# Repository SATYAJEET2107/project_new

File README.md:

# project_new
second circuit design board

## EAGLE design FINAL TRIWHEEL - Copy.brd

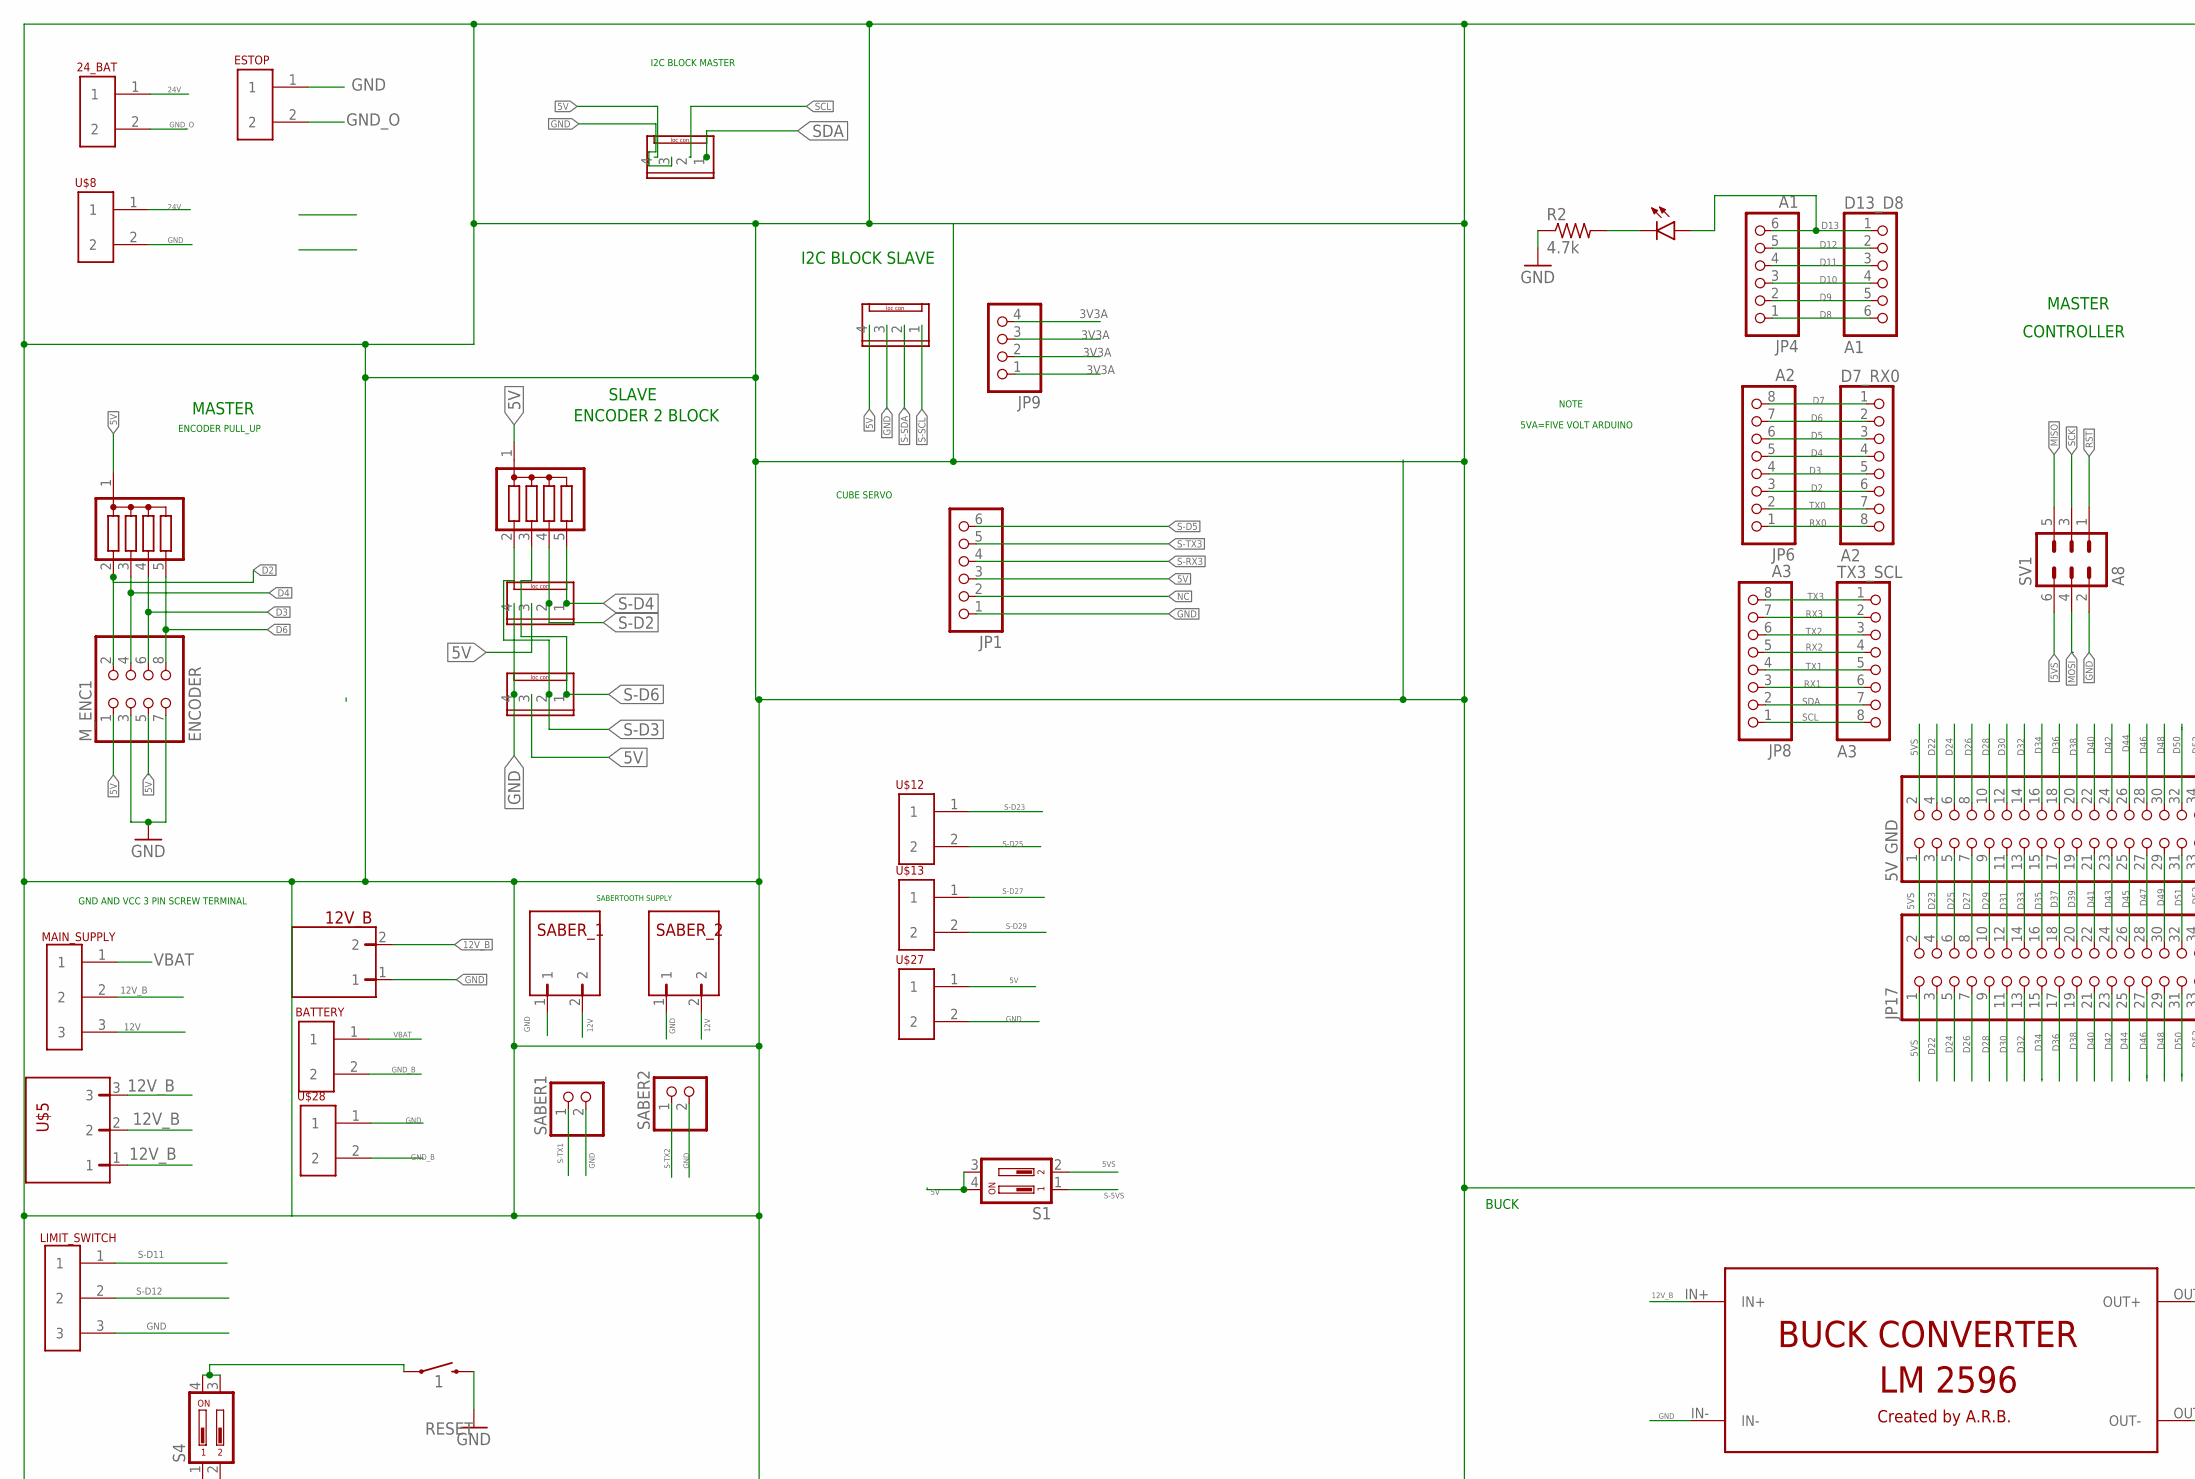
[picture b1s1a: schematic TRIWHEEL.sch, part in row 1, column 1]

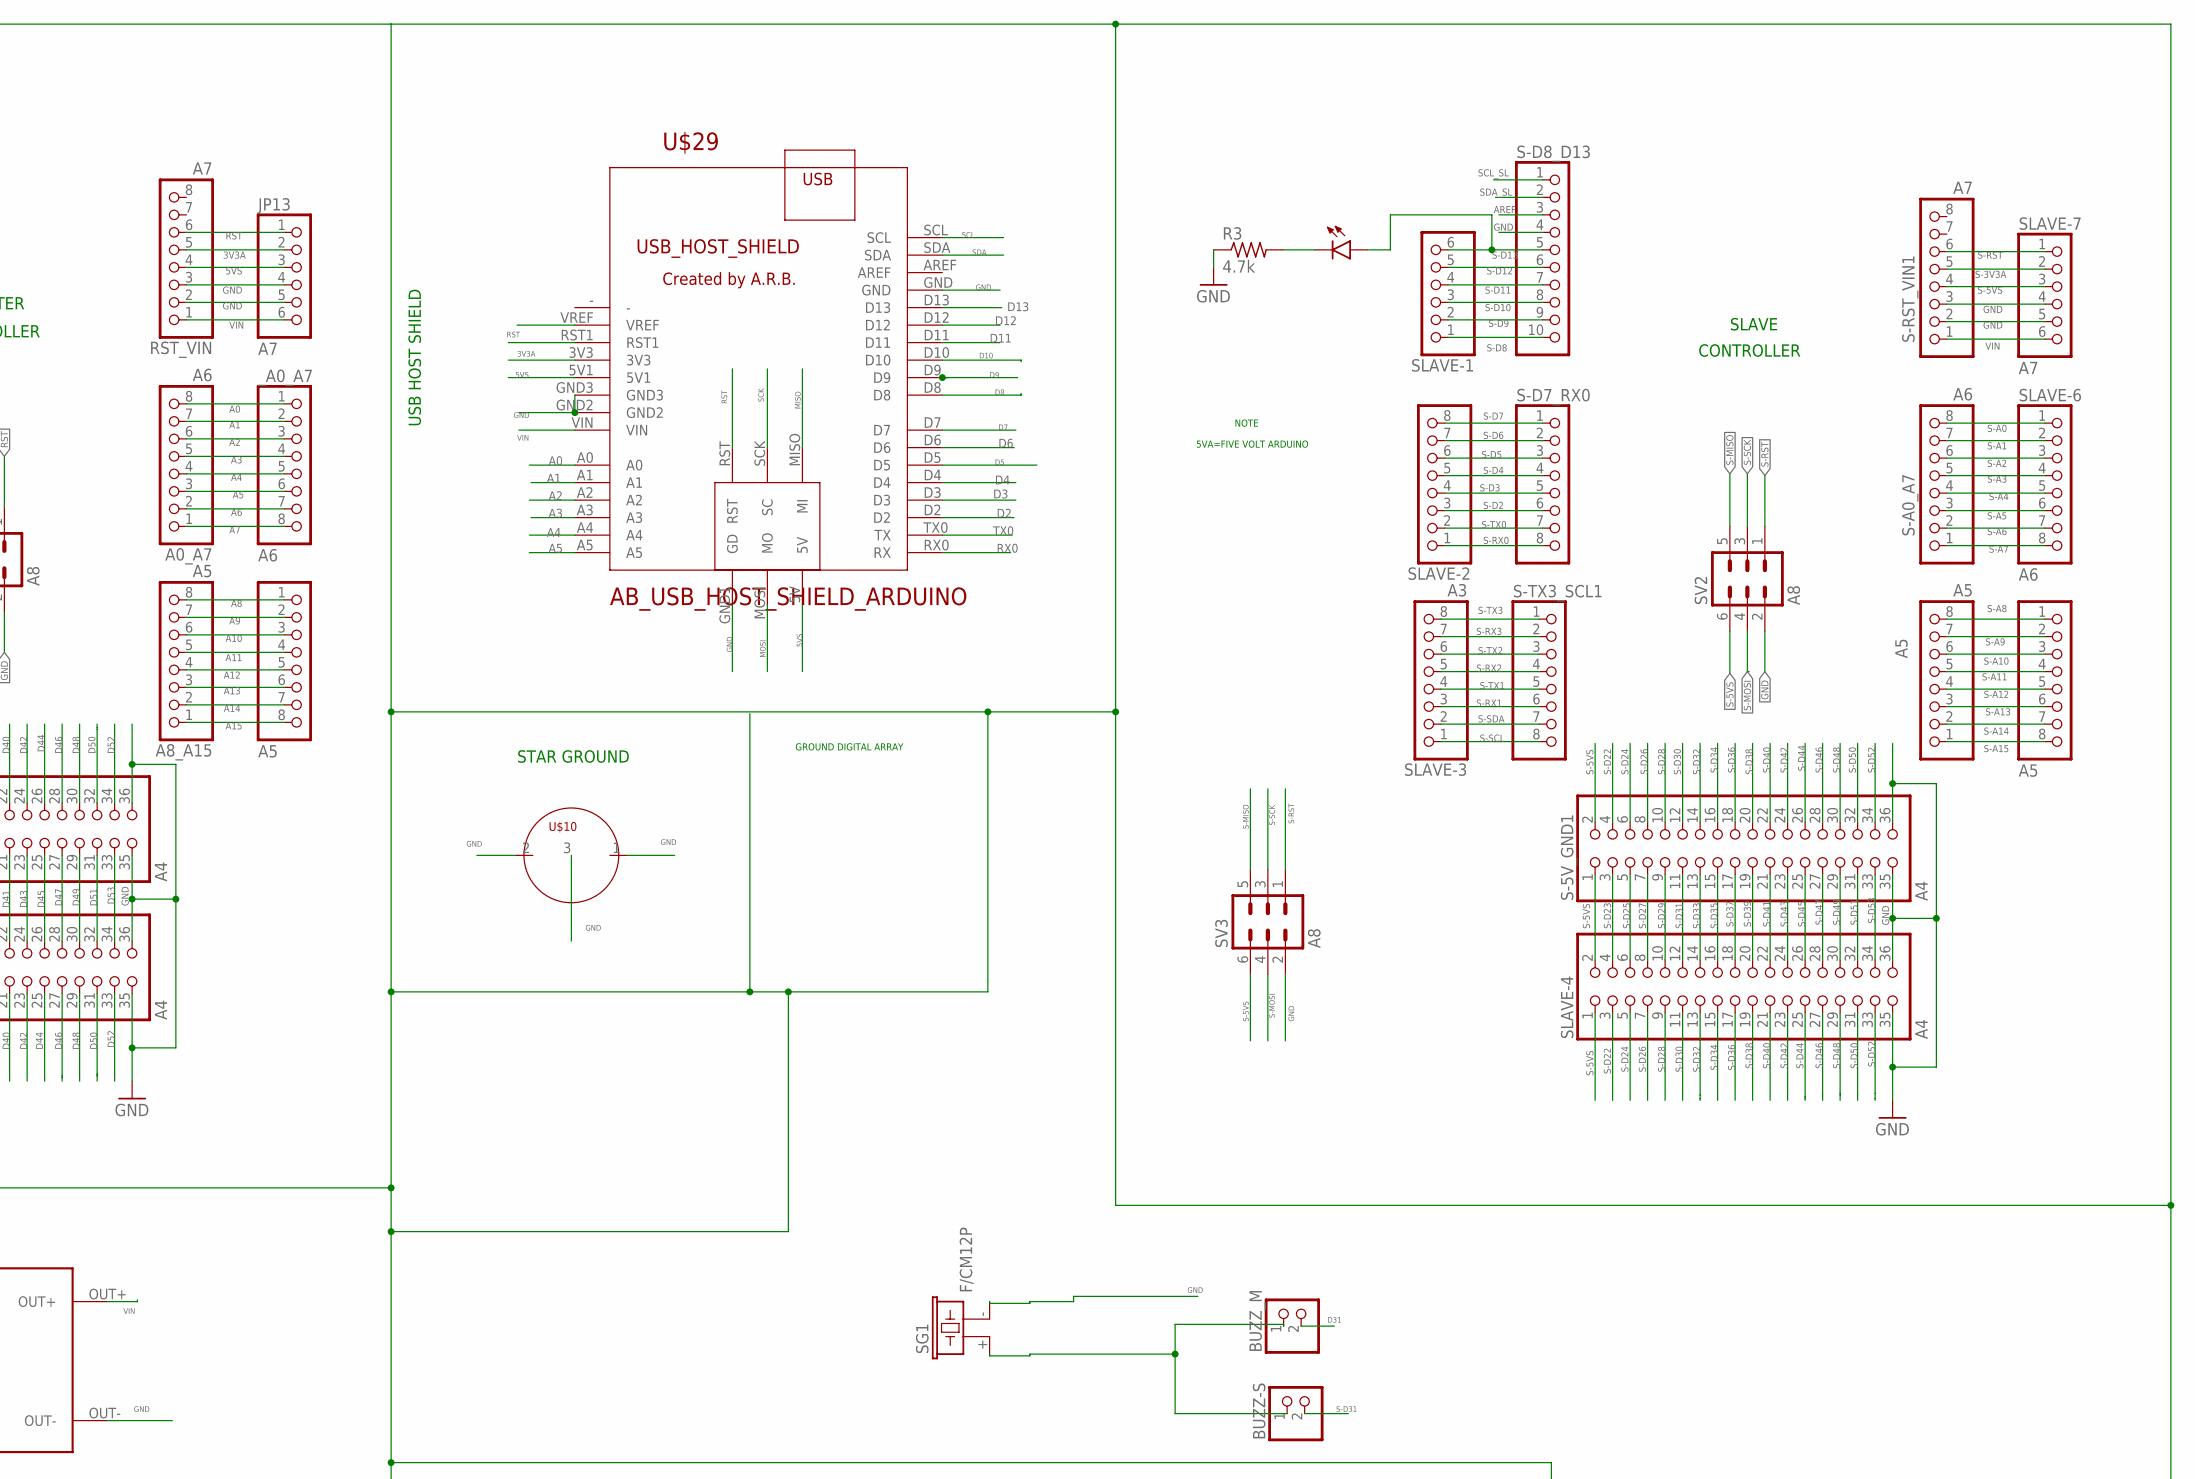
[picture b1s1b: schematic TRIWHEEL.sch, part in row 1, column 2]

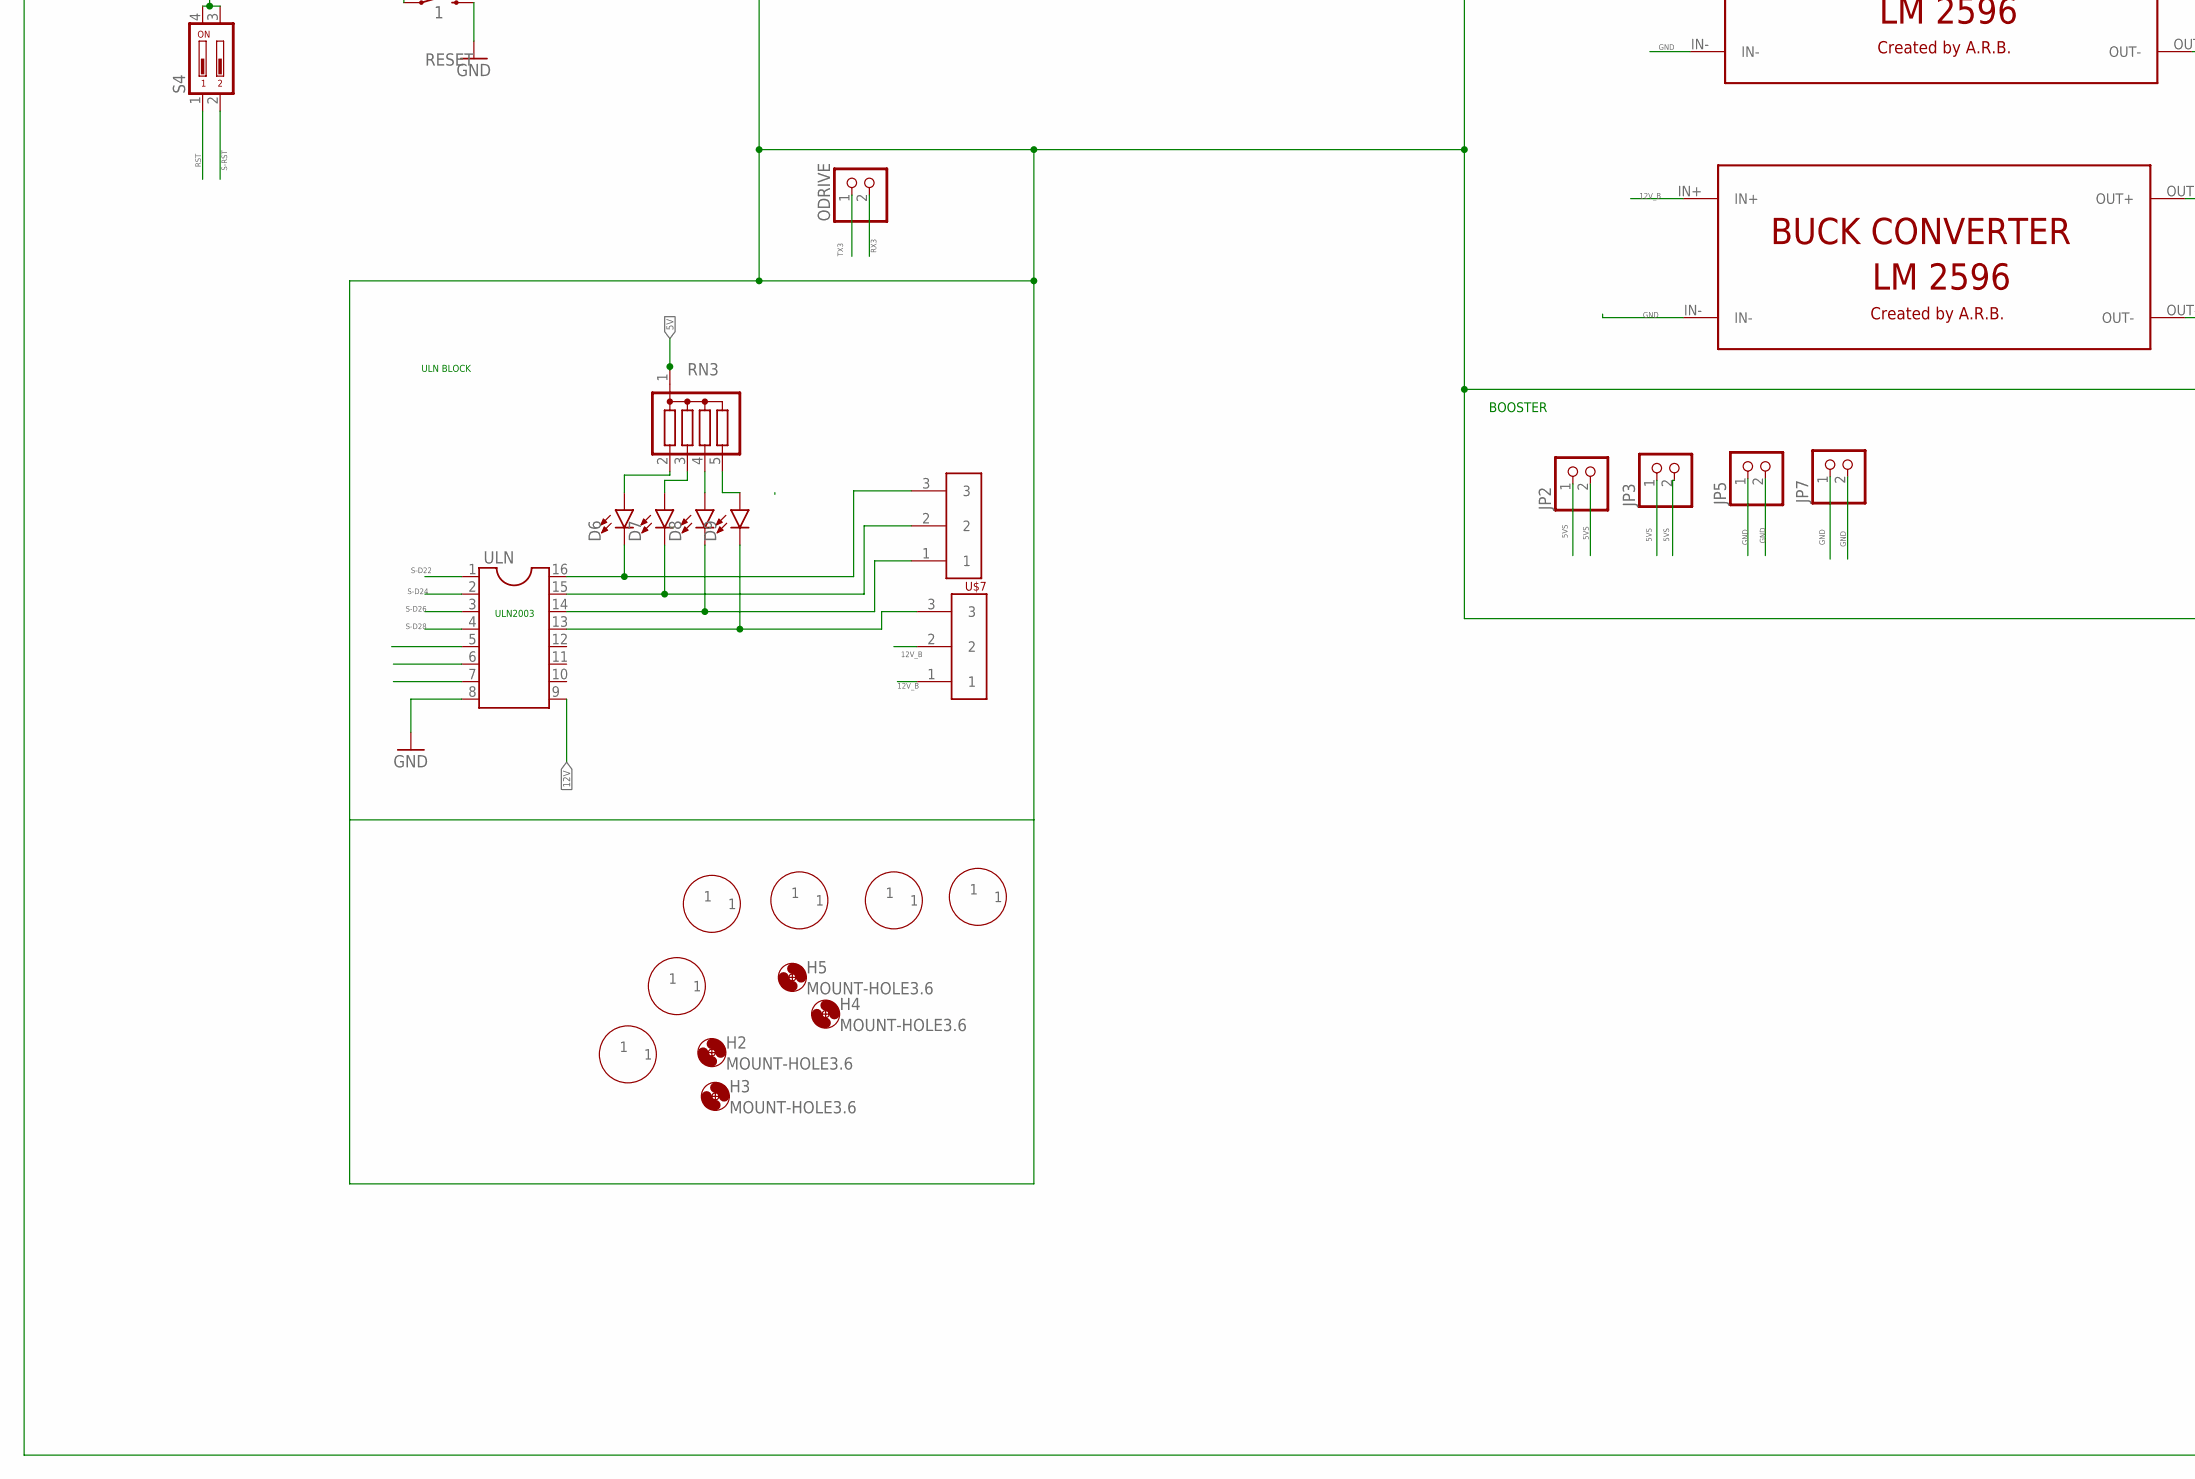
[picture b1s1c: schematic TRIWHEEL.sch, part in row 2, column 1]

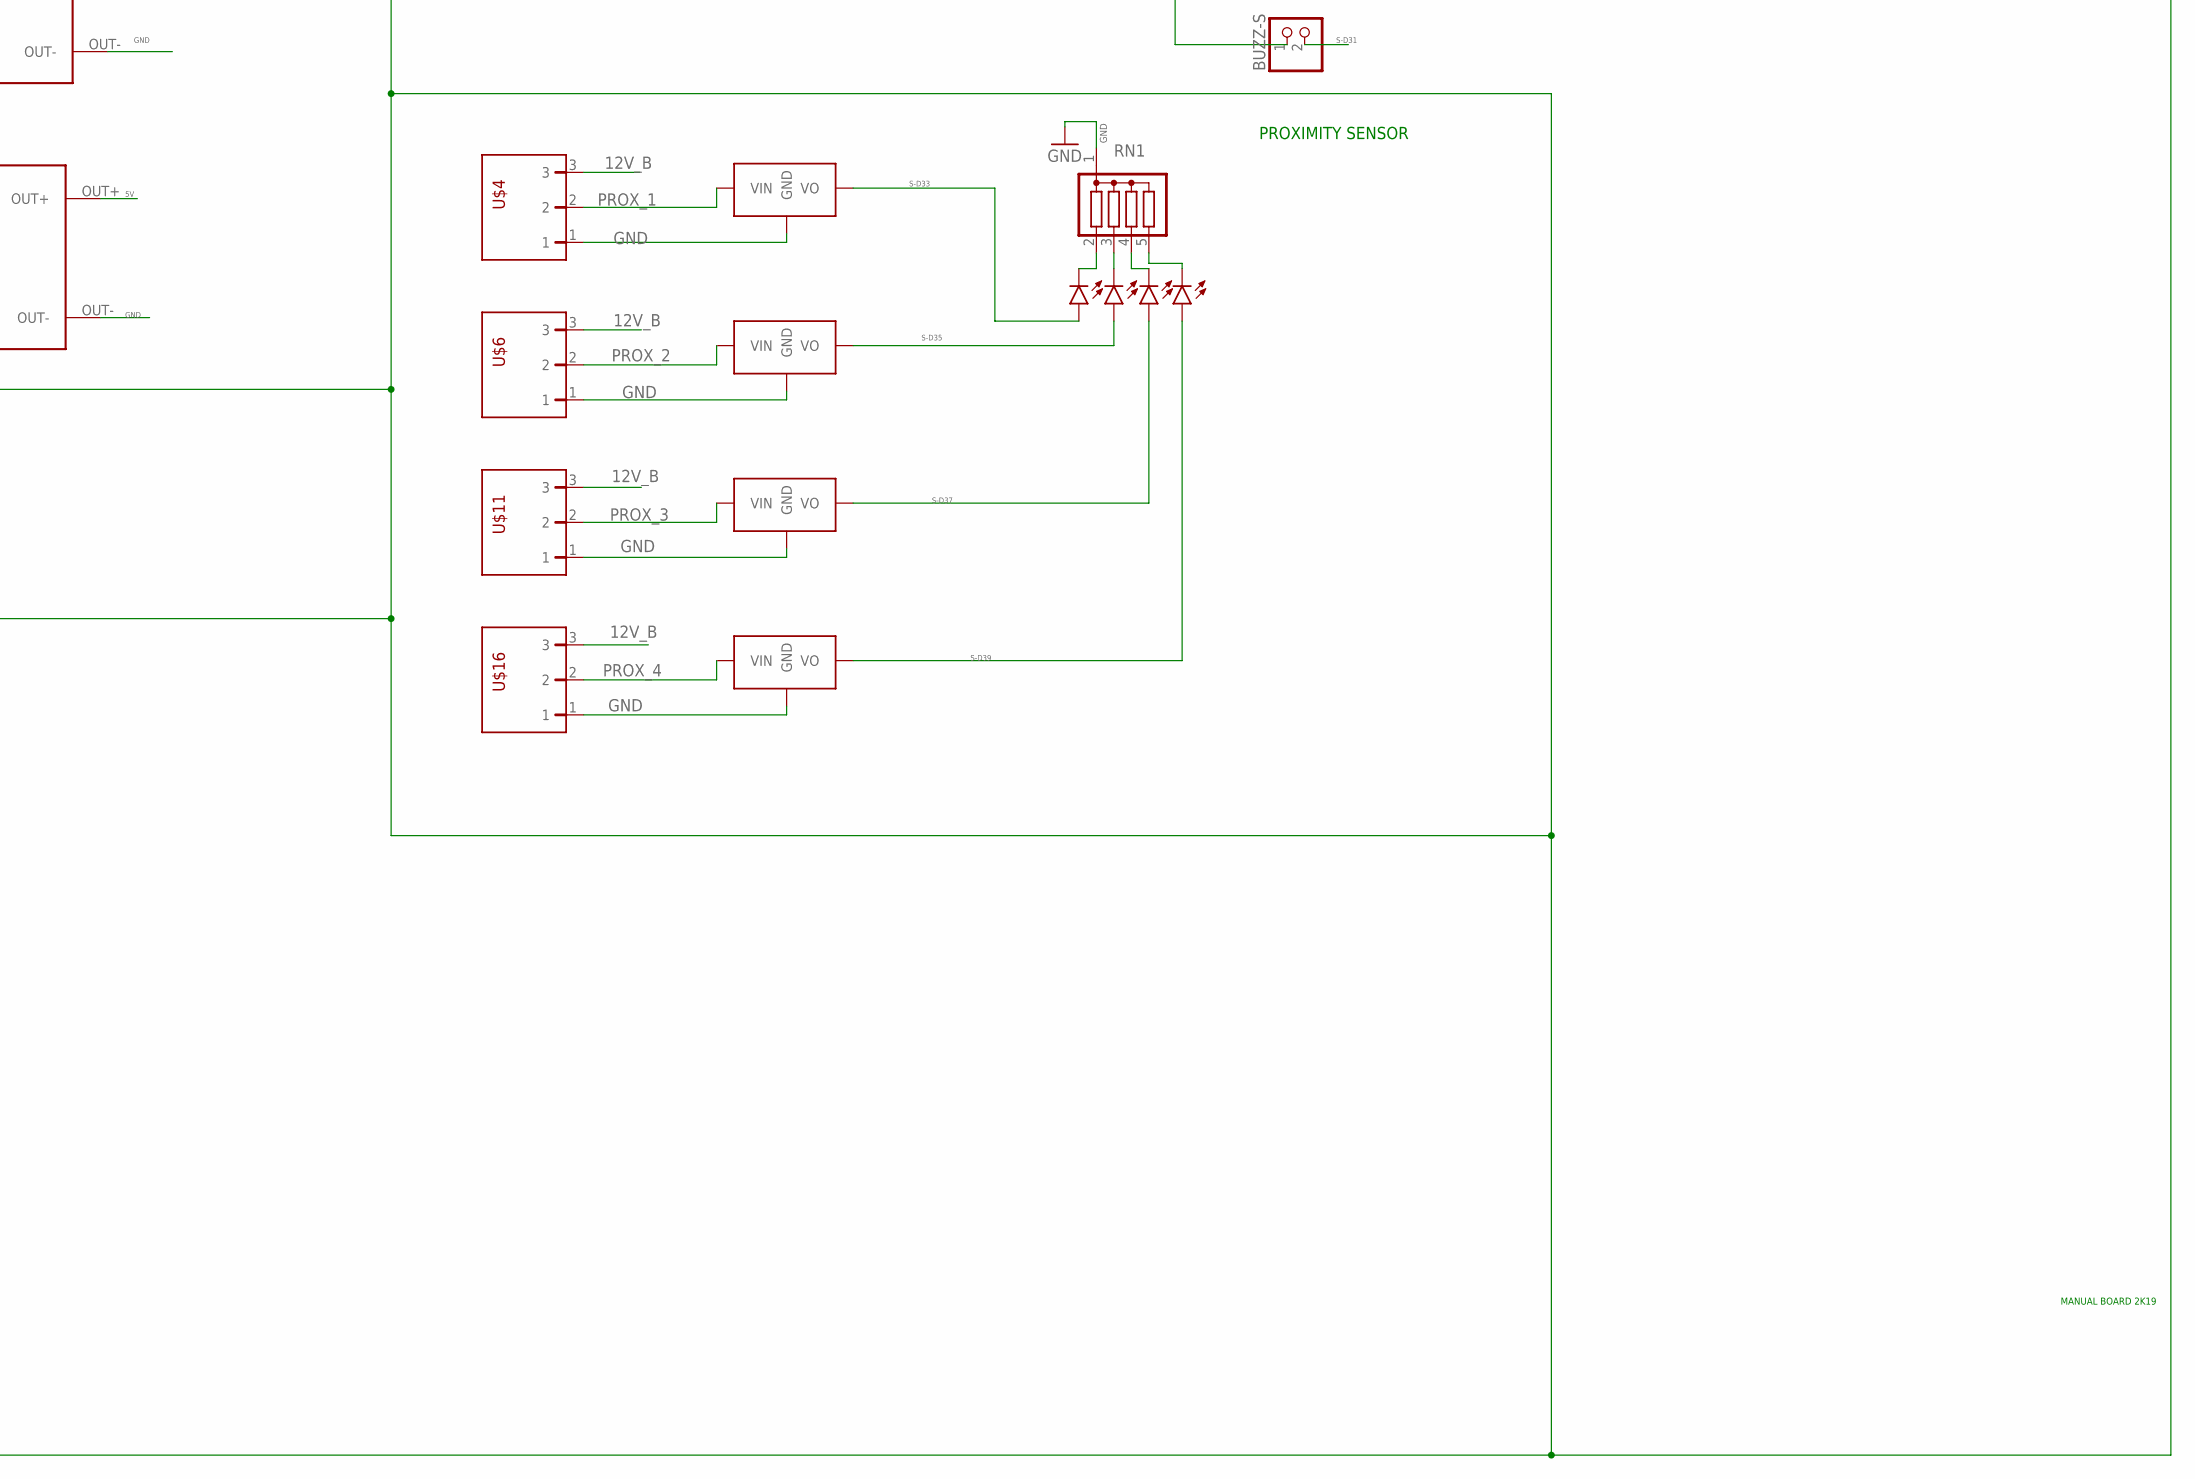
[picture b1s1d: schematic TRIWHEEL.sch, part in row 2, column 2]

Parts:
5V_GND: A4; 2X18
12V_B: AB_RIGHT_TER_BLK
24_BAT: AB_SCREW_TERMINAL_5MM_2PIN
A0_A7: A6; 1X08
A5, A8_A15: A5; 1X08
BATTERY: AB_SCREW_TERMINAL_5MM_2PIN
BUZZ-S: PINHD-1X2; 1X02
BUZZ_M: PINHD-1X2; 1X02
D1, D2, D3, D4, D5, D6, D7, D8, D9, D13: LED-3MM-NO_SILK; LED_3MM-NS
D7_RX0: A2; 1X08
D13_D8: A1; 1X06
ESTOP: AB_SCREW_TERMINAL_5MM_2PIN
H2, H3, H4, H5: MOUNT-HOLE3.6; 3,6
IMU_BLOCK: AB_4PIN_LOC_CONNECTOR
IMU_BLOCK-M: AB_4PIN_LOC_CONNECTOR
JP: A5; 1X08
JP1: PINHD-1X6; 1X06
JP2, JP3, JP5, JP7: PINHD-1X2; 1X02
JP4: A1; 1X06
JP6: A2; 1X08
JP8: A3; 1X08
JP9: PINHD-1X4; 1X04
JP13: A7; 1X06
JP17: A4; 2X18
LIMIT_SWITCH: AB_SCREW_TER_5MM_3PIN
MAIN_SUPPLY, MAIN_SUPPLY1: AB_SCREW_TER_5MM_3PIN
M_ENC1: ENCODER; 2X04
ODRIVE: PINHD-1X2; 1X02
PULL_RESISTOR-M: G04R; SIL5
R2, R3: 4.7k; 0204/7
RESET: 1; TACTILE_SWITCH_PTH_6.0MM
RN1, RN3: G04R; SIL5
RST_VIN: A7; 1X08
S1, S4: DIP02YL
S-5V_GND1: A4; 2X18
S-A0_A7: A6; 1X08
S-D7_RX0: A2; 1X08
S-D8_D13: PINHD-1X10; 1X10
S-ENC: G04R; SIL5
S-RST_VIN1: A7; 1X08
S-TX3_SCL1: A3; 1X08
SABER1, SABER2: PINHD-1X2; 1X02
SABER_1, SABER_2: AB_RIGHT_TER_BLK
SG1: F/CM12P
SLAVE-1: A1; 1X06
SLAVE-2: A2; 1X08
SLAVE-3: A3; 1X08
SLAVE-4: A4; 2X18
SLAVE-6: A6; 1X08
SLAVE-7: A7; 1X06
SV1, SV2, SV3: A8; MA03-2
S_A8_A15: A5; 1X08
TX3_SCL: A3; 1X08
U$1, U$2: AB_LM2596_BUCK_CONVERTER
U$4, U$5, U$6, U$11, U$16: AB_RIGHT_TER_BLK_3PIN
U$7: AB_SCREW_TER_5MM_3PIN
U$8, U$12, U$13, U$27, U$28: AB_SCREW_TERMINAL_5MM_2PIN
U$9, U$15, U$23, U$24, U$25, U$26: AB_PLATED_DRILL_160MIL
U$10: AB_JOINT_GND
U$17, U$18, U$19, U$20: AB_7805_FLAT
U$21: en1; AB_4PIN_LOC_CONNECTOR
U$22: en2; AB_4PIN_LOC_CONNECTOR
U$29: AB_USB_HOST_SHIELD_ARDUINO
ULN: DIL16
_A0_A7: A6; 1X08

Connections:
3V3A: JP9.1, JP9.2, JP9.3, JP9.4, JP13.2, RST_VIN.5, U$29.3V3
5V: IMU_BLOCK.4, IMU_BLOCK-M.4, JP1.3, M_ENC1.1, M_ENC1.5, PULL_RESISTOR-M.1, RN3.1, S1.3, S1.4, S-ENC.1, U$2.OUT+, U$21.3, U$22.3, U$27.1; also elsewhere on the board
5VS: 5V_GND.1, 5V_GND.2, JP2.1, JP2.2, JP3.1, JP3.2, JP13.3, JP17.1, JP17.2, RST_VIN.4, S1.2, SV1.6, U$29.5V, U$29.5V1
12V: MAIN_SUPPLY.3, SABER_1.2, SABER_2.2, ULN.9
12V_B: 12V_B.2, MAIN_SUPPLY.2, MAIN_SUPPLY1.1, MAIN_SUPPLY1.2, U$1.IN+, U$2.IN+, U$4.3, U$5.1, U$5.2, U$5.3, U$6.3, U$11.3, U$16.3
24V: 24_BAT.1, U$8.1
A0: A0_A7.8, U$29.A0, _A0_A7.1
A1: A0_A7.7, U$29.A1, _A0_A7.2
A2: A0_A7.6, U$29.A2, _A0_A7.3
A3: A0_A7.5, U$29.A3, _A0_A7.4
A4: A0_A7.4, U$29.A4, _A0_A7.5
A5: A0_A7.3, U$29.A5, _A0_A7.6
A6: A0_A7.2, _A0_A7.7
A7: A0_A7.1, _A0_A7.8
A8: A8_A15.8, JP.1
A9: A8_A15.7, JP.2
A10: A8_A15.6, JP.3
A11: A8_A15.5, JP.4
A12: A8_A15.4, JP.5
A13: A8_A15.3, JP.6
A14: A8_A15.2, JP.7
A15: A8_A15.1, JP.8
AREF: S-D8_D13.3
D2: D7_RX0.6, JP6.3, M_ENC1.2, PULL_RESISTOR-M.2, U$29.D2; also elsewhere on the board
D3: D7_RX0.5, JP6.4, M_ENC1.6, PULL_RESISTOR-M.4, U$29.D3; also elsewhere on the board
D4: D7_RX0.4, JP6.5, M_ENC1.4, PULL_RESISTOR-M.3, U$29.D4; also elsewhere on the board
D5: D7_RX0.3, JP6.6, U$29.D5
D6: D7_RX0.2, JP6.7, M_ENC1.8, PULL_RESISTOR-M.5, U$29.D6; also elsewhere on the board
D7: D7_RX0.1, JP6.8, U$29.D7
D8: D13_D8.6, JP4.1, U$29.D8
D9: D13_D8.5, JP4.2, U$29.D9
D10: D13_D8.4, JP4.3, U$29.D10
D11: D13_D8.3, JP4.4, U$29.D11
D12: D13_D8.2, JP4.5, U$29.D12
D13: D13.A, D13_D8.1, JP4.6, U$29.D13
D22: 5V_GND.4, JP17.3
D23: 5V_GND.3, JP17.4
D24: 5V_GND.6, JP17.5
D25: 5V_GND.5, JP17.6
D26: 5V_GND.8, JP17.7
D27: 5V_GND.7, JP17.8
D28: 5V_GND.10, JP17.9
D29: 5V_GND.9, JP17.10
D30: 5V_GND.12, JP17.11
D31: 5V_GND.11, BUZZ_M.2, JP17.12
D32: 5V_GND.14, JP17.13
D33: 5V_GND.13, JP17.14
D34: 5V_GND.16, JP17.15
D35: 5V_GND.15, JP17.16
D36: 5V_GND.18, JP17.17
D37: 5V_GND.17, JP17.18
D38: 5V_GND.20, JP17.19
D39: 5V_GND.19, JP17.20
D40: 5V_GND.22, JP17.21
D41: 5V_GND.21, JP17.22
D42: 5V_GND.24, JP17.23
D43: 5V_GND.23, JP17.24
D44: 5V_GND.26, JP17.25
D45: 5V_GND.25, JP17.26
D46: 5V_GND.28, JP17.27
D47: 5V_GND.27, JP17.28
D48: 5V_GND.30, JP17.29
D49: 5V_GND.29, JP17.30
D50: 5V_GND.32, JP17.31
D51: 5V_GND.31, JP17.32
D52: 5V_GND.34, JP17.33
D53: 5V_GND.33, JP17.34
GND: 5V_GND.35, 5V_GND.36, 12V_B.1, ESTOP.1, IMU_BLOCK.3, IMU_BLOCK-M.3, JP1.1, JP5.1, JP5.2, JP7.1, JP7.2, JP13.4, JP13.5, JP17.35, JP17.36, LIMIT_SWITCH.3, M_ENC1.3, M_ENC1.7, R2.1, R3.1, RESET.3 (2), RN1.1, RST_VIN.2, RST_VIN.3, S-5V_GND1.35, S-5V_GND1.36, S-D8_D13.4, S-RST_VIN1.2, S-RST_VIN1.3, SABER1.2, SABER2.2, SABER_1.1, SABER_2.1, SG1.- (2), SLAVE-4.35, SLAVE-4.36, SLAVE-7.4, SLAVE-7.5, SV1.2, SV2.2, SV3.2, U$1.IN-, U$1.OUT-, U$2.IN-, U$2.OUT-, U$4.1, U$6.1, U$8.2, U$10.1, U$10.2, U$10.3, U$11.1, U$16.1, U$17.2 (GND), U$18.2 (GND), U$19.2 (GND), U$20.2 (GND), U$21.4, U$22.4, U$27.2, U$28.1, U$29.GND, U$29.GND1 (GD), U$29.GND2, U$29.GND3, ULN.8; also elsewhere on the board
GND_B: BATTERY.2, U$28.2
GND_O: 24_BAT.2, ESTOP.2
MISO: SV1.5, U$29.MISO (MI)
MOSI: SV1.4, U$29.MOSI (MO)
unnamed: D5.K (C), R3.2
unnamed: BUZZ-S.1, BUZZ_M.1, SG1.+ (1)
unnamed: D1.K (C), RN1.2
unnamed: D2.K (C), RN1.3
unnamed: D6.K (C), U$7.3, ULN.16
unnamed: D7.K (C), U$7.2, ULN.15
unnamed: D8.K (C), U$7.1, ULN.14
unnamed: D9.K (C), MAIN_SUPPLY1.3, ULN.13
unnamed: D6.A, RN3.2
unnamed: D7.A, RN3.3
unnamed: D8.A, RN3.4
unnamed: D9.A, RN3.5
unnamed: RESET.1, S4.3, S4.4
unnamed: D3.K (C), RN1.4
unnamed: D4.K (C), RN1.5
unnamed: D13.K (C), R2.2
NC: JP1.2
PROX_1: U$4.2, U$17.1 (VIN)
PROX_2: U$6.2, U$18.1 (VIN)
PROX_3: U$11.2, U$19.1 (VIN)
PROX_4: U$16.2, U$20.1 (VIN)
RST: JP13.1, RST_VIN.6, S4.1, SV1.1, U$29.RST, U$29.RST1
RX0: D7_RX0.8, JP6.1, U$29.RX0 (RX)
RX1: JP8.3, TX3_SCL.6
RX2: JP8.5, TX3_SCL.4
RX3: JP8.7, ODRIVE.2, TX3_SCL.2
S-3V3A: S-RST_VIN1.5, SLAVE-7.2
S-5VS: S1.1, S-5V_GND1.1, S-5V_GND1.2, S-RST_VIN1.4, SLAVE-4.1, SLAVE-4.2, SLAVE-7.3, SV2.6, SV3.6
S-A0: S-A0_A7.8, SLAVE-6.1
S-A1: S-A0_A7.7, SLAVE-6.2
S-A2: S-A0_A7.6, SLAVE-6.3
S-A3: S-A0_A7.5, SLAVE-6.4
S-A4: S-A0_A7.4, SLAVE-6.5
S-A5: S-A0_A7.3, SLAVE-6.6
S-A6: S-A0_A7.2, SLAVE-6.7
S-A7: S-A0_A7.1, SLAVE-6.8
S-A8: A5.8, S_A8_A15.1
S-A9: A5.7, S_A8_A15.2
S-A10: A5.6, S_A8_A15.3
S-A11: A5.5, S_A8_A15.4
S-A12: A5.4, S_A8_A15.5
S-A13: A5.3, S_A8_A15.6
S-A14: A5.2, S_A8_A15.7
S-A15: A5.1, S_A8_A15.8
S-D2: S-D7_RX0.6, S-ENC.4, SLAVE-2.3, U$21.2
S-D3: S-D7_RX0.5, S-ENC.2, SLAVE-2.4, U$22.2
S-D4: S-D7_RX0.4, S-ENC.5, SLAVE-2.5, U$21.1
S-D5: JP1.6, S-D7_RX0.3, SLAVE-2.6
S-D6: S-D7_RX0.2, S-ENC.3, SLAVE-2.7, U$22.1
S-D7: S-D7_RX0.1, SLAVE-2.8
S-D8: S-D8_D13.10, SLAVE-1.1
S-D9: S-D8_D13.9, SLAVE-1.2
S-D10: S-D8_D13.8, SLAVE-1.3
S-D11: LIMIT_SWITCH.1, S-D8_D13.7, SLAVE-1.4
S-D12: LIMIT_SWITCH.2, S-D8_D13.6, SLAVE-1.5
S-D13: D5.A, S-D8_D13.5, SLAVE-1.6
S-D22: S-5V_GND1.4, SLAVE-4.3, ULN.1
S-D23: S-5V_GND1.3, SLAVE-4.4, U$12.1
S-D24: S-5V_GND1.6, SLAVE-4.5, ULN.2
S-D25: S-5V_GND1.5, SLAVE-4.6, U$12.2
S-D26: S-5V_GND1.8, SLAVE-4.7, ULN.3
S-D27: S-5V_GND1.7, SLAVE-4.8, U$13.1
S-D28: S-5V_GND1.10, SLAVE-4.9, ULN.4
S-D29: S-5V_GND1.9, SLAVE-4.10, U$13.2
S-D30: S-5V_GND1.12, SLAVE-4.11
S-D31: BUZZ-S.2, S-5V_GND1.11, SLAVE-4.12
S-D32: S-5V_GND1.14, SLAVE-4.13
S-D33: D1.A, S-5V_GND1.13, SLAVE-4.14, U$17.3 (VO)
S-D34: S-5V_GND1.16, SLAVE-4.15
S-D35: D2.A, S-5V_GND1.15, SLAVE-4.16, U$18.3 (VO)
S-D36: S-5V_GND1.18, SLAVE-4.17
S-D37: D3.A, S-5V_GND1.17, SLAVE-4.18, U$19.3 (VO)
S-D38: S-5V_GND1.20, SLAVE-4.19
S-D39: D4.A, S-5V_GND1.19, SLAVE-4.20, U$20.3 (VO)
S-D40: S-5V_GND1.22, SLAVE-4.21
S-D41: S-5V_GND1.21, SLAVE-4.22
S-D42: S-5V_GND1.24, SLAVE-4.23
S-D43: S-5V_GND1.23, SLAVE-4.24
S-D44: S-5V_GND1.26, SLAVE-4.25
S-D45: S-5V_GND1.25, SLAVE-4.26
S-D46: S-5V_GND1.28, SLAVE-4.27
S-D47: S-5V_GND1.27, SLAVE-4.28
S-D48: S-5V_GND1.30, SLAVE-4.29
S-D49: S-5V_GND1.29, SLAVE-4.30
S-D50: S-5V_GND1.32, SLAVE-4.31
S-D51: S-5V_GND1.31, SLAVE-4.32
S-D52: S-5V_GND1.34, SLAVE-4.33
S-D53: S-5V_GND1.33, SLAVE-4.34
S-MISO: SV2.5, SV3.5
S-MOSI: SV2.4, SV3.4
S-RST: S4.2, S-RST_VIN1.6, SLAVE-7.1, SV2.1, SV3.1
S-RX0: S-D7_RX0.8, SLAVE-2.1
S-RX1: S-TX3_SCL1.6, SLAVE-3.3
S-RX2: S-TX3_SCL1.4, SLAVE-3.5
S-RX3: JP1.4, S-TX3_SCL1.2, SLAVE-3.7
S-SCK: SV2.3, SV3.3
S-SCL: IMU_BLOCK.1, S-TX3_SCL1.8, SLAVE-3.1; also elsewhere on the board
S-SDA: IMU_BLOCK.2, S-TX3_SCL1.7, SLAVE-3.2; also elsewhere on the board
S-TX0: S-D7_RX0.7, SLAVE-2.2
S-TX1: S-TX3_SCL1.5, SABER1.1, SLAVE-3.4
S-TX2: S-TX3_SCL1.3, SABER2.1, SLAVE-3.6
S-TX3: JP1.5, S-TX3_SCL1.1, SLAVE-3.8
SCK: SV1.3, U$29.SCK (SC)
SCL: IMU_BLOCK-M.2, JP8.1, TX3_SCL.8, U$29.SCL; also elsewhere on the board
SCL_SL: S-D8_D13.1
SDA: IMU_BLOCK-M.1, JP8.2, TX3_SCL.7, U$29.SDA; also elsewhere on the board
SDA_SL: S-D8_D13.2
TX0: D7_RX0.7, JP6.2, U$29.TX0 (TX)
TX1: JP8.4, TX3_SCL.5
TX2: JP8.6, TX3_SCL.3
TX3: JP8.8, ODRIVE.1, TX3_SCL.1
VBAT: BATTERY.1, MAIN_SUPPLY.1
VIN: JP13.6, RST_VIN.1, S-RST_VIN1.1, SLAVE-7.6, U$1.OUT+, U$29.VIN

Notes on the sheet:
ULN2003
I2C BLOCK MASTER
CONTROLLER
5VA=FIVE VOLT ARDUINO
NOTE
ENCODER PULL_UP
GND AND VCC 3 PIN SCREW TERMINAL
ULN BLOCK
USB HOST SHIELD
MANUAL BOARD 2K19
CUBE SERVO
SABERTOOTH SUPPLY
BUCK
BOOSTER
STAR GROUND
ENCODER 2 BLOCK
I2C BLOCK SLAVE
GROUND DIGITAL ARRAY
SLAVE
MASTER
PROXIMITY SENSOR

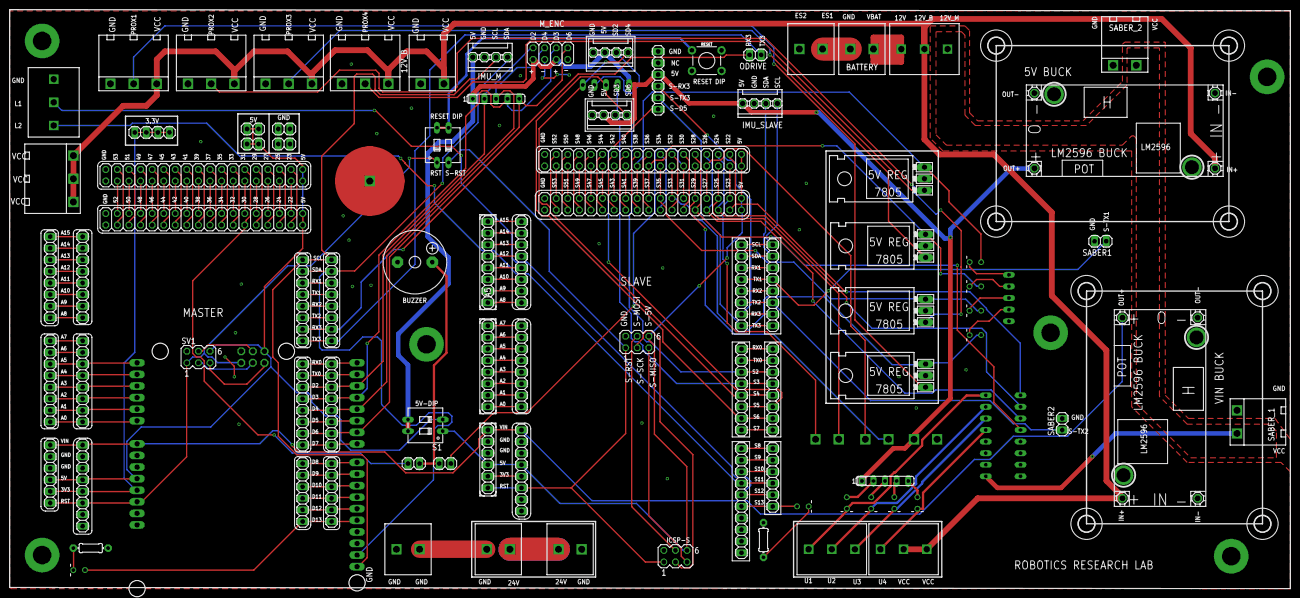
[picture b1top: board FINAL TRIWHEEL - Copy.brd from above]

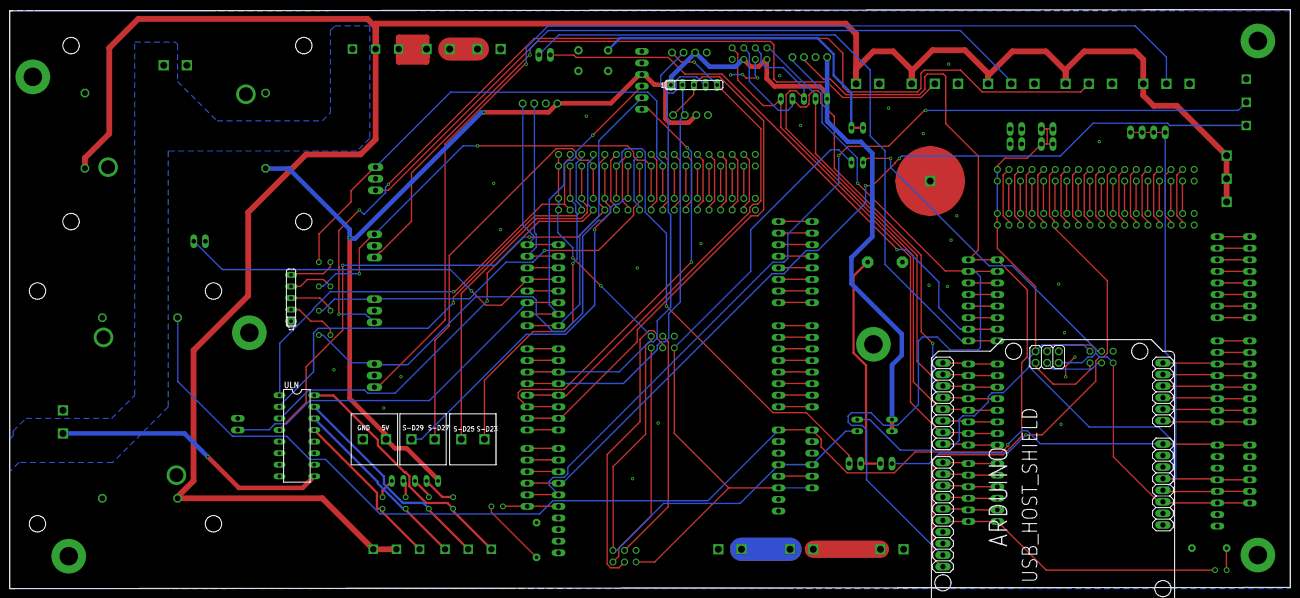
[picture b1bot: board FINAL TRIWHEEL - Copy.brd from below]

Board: 2 copper layers, 280.9 x 127.0 mm, 110 parts (7 on the bottom side), 181 nets.

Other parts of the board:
H1, H6, H7, H8: MOUNT-HOLE3.6; 3,6
IMU_M: AB_4PIN_LOC_CONNECTOR
IMU_SLAVE: AB_4PIN_LOC_CONNECTOR
M_ENC: ENCODER; 2X04

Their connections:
5V: IMU_M.4, IMU_SLAVE.4, M_ENC.1, M_ENC.5; also elsewhere on the board
D2: M_ENC.2; also elsewhere on the board
D3: M_ENC.6; also elsewhere on the board
D4: M_ENC.4; also elsewhere on the board
D6: M_ENC.8; also elsewhere on the board
GND: IMU_M.3, IMU_SLAVE.3, M_ENC.3, M_ENC.7; also elsewhere on the board
S-SCL: IMU_SLAVE.1; also elsewhere on the board
S-SDA: IMU_SLAVE.2; also elsewhere on the board
SCL: IMU_M.2; also elsewhere on the board
SDA: IMU_M.1; also elsewhere on the board

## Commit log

2020-05-12 new project done

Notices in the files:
parts and their libraries:
SparkFun-LED: Licensing: Creative Commons ShareAlike 4.0 International - https://creativecommons.org/licenses/by-sa/4.0
